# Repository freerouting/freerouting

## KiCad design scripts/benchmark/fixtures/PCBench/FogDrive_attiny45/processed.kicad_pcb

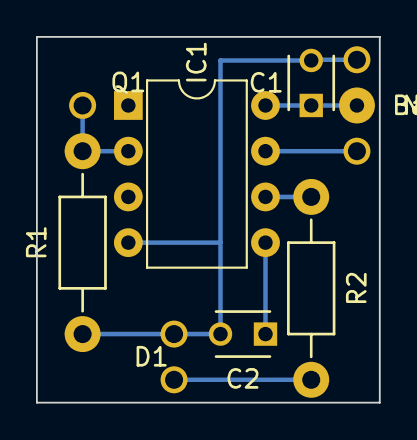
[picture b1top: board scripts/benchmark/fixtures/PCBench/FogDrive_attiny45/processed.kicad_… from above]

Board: 2 copper layers, 19.0 x 20.3 mm, 9 parts (0 on the bottom side), 7 nets.

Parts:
Bat+: SolderWirePad_single_0-8mmDrill
C1, C2: 10nF; C_Disc_D3_P2.5
D1: low current LED; WireConnection_1.50mmDrill
IC1: ATTINY45-P; DIP-8_W7.62mm
Noname_1: Button; WireConnection_1.50mmDrill
Q1: RLB3034; WireConnection_1.50mmDrill
R1: 22kΩ; Resistor_Horizontal_RM10mm
R2: 100Ω; Resistor_Horizontal_RM10mm

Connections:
+BATT: C1.1, IC1.8
/Mira/AREF: C2.1, IC1.5
/Mira/BUTTON: IC1.7, Noname_1.2
/Mira/FIRE: IC1.2, Q1.2, R1.1
/Mira/LED: IC1.6, R2.2
GND: C1.2, C2.2, D1.1, IC1.4, Noname_1.1, R1.2
unnamed: D1.2, R2.1

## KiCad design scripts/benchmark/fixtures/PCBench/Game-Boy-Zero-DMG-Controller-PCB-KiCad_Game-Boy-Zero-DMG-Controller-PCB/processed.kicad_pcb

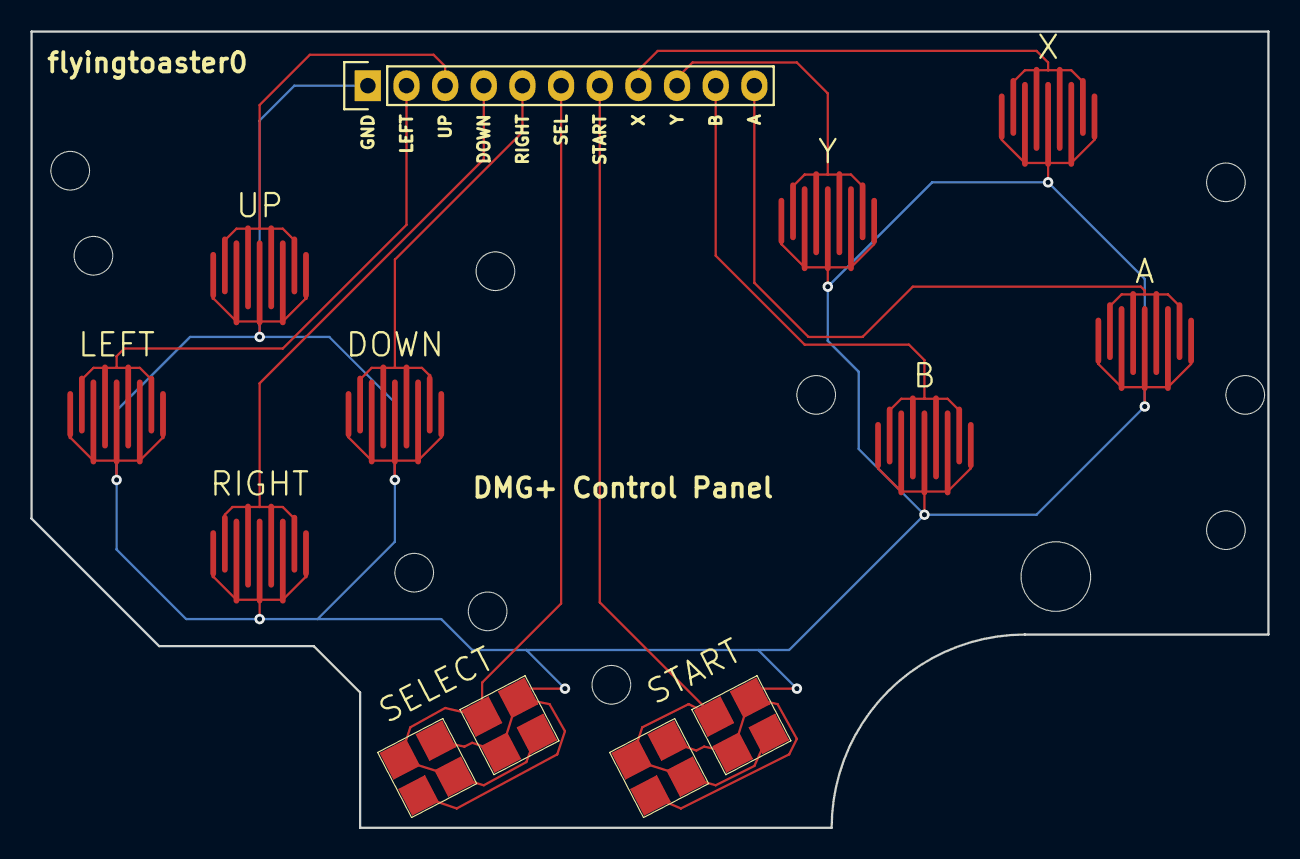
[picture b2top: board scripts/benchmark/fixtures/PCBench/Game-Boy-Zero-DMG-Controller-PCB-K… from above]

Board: 2 copper layers, 81.3 x 52.3 mm, 11 parts (0 on the bottom side), 11 nets.

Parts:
P1: CONN_01X11; Socket_Strip_Straight_1x11
SW1: LEFT; GameBoy-DMG-BTN
SW2: UP; GameBoy-DMG-BTN
SW3: DOWN; GameBoy-DMG-BTN
SW4: RIGHT; GameBoy-DMG-BTN
SW5: SELECT; GameBoy-DMG-START-SEL
SW6: START; GameBoy-DMG-START-SEL
SW7: X; GameBoy-DMG-BTN
SW8: Y; GameBoy-DMG-BTN
SW9: B; GameBoy-DMG-BTN
SW10: A; GameBoy-DMG-BTN

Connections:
GND: P1.1, SW1.1, SW2.1, SW3.1, SW4.1, SW5.1, SW6.1, SW7.1, SW8.1, SW9.1, SW10.1
unnamed: P1.2, SW1.2
unnamed: P1.3, SW2.2
unnamed: P1.4, SW4.2
unnamed: P1.5, SW3.2
unnamed: P1.6, SW5.2
unnamed: P1.7, SW6.2
unnamed: P1.8, SW7.2
unnamed: P1.9, SW8.2
unnamed: P1.10, SW9.2
unnamed: P1.11, SW10.2
